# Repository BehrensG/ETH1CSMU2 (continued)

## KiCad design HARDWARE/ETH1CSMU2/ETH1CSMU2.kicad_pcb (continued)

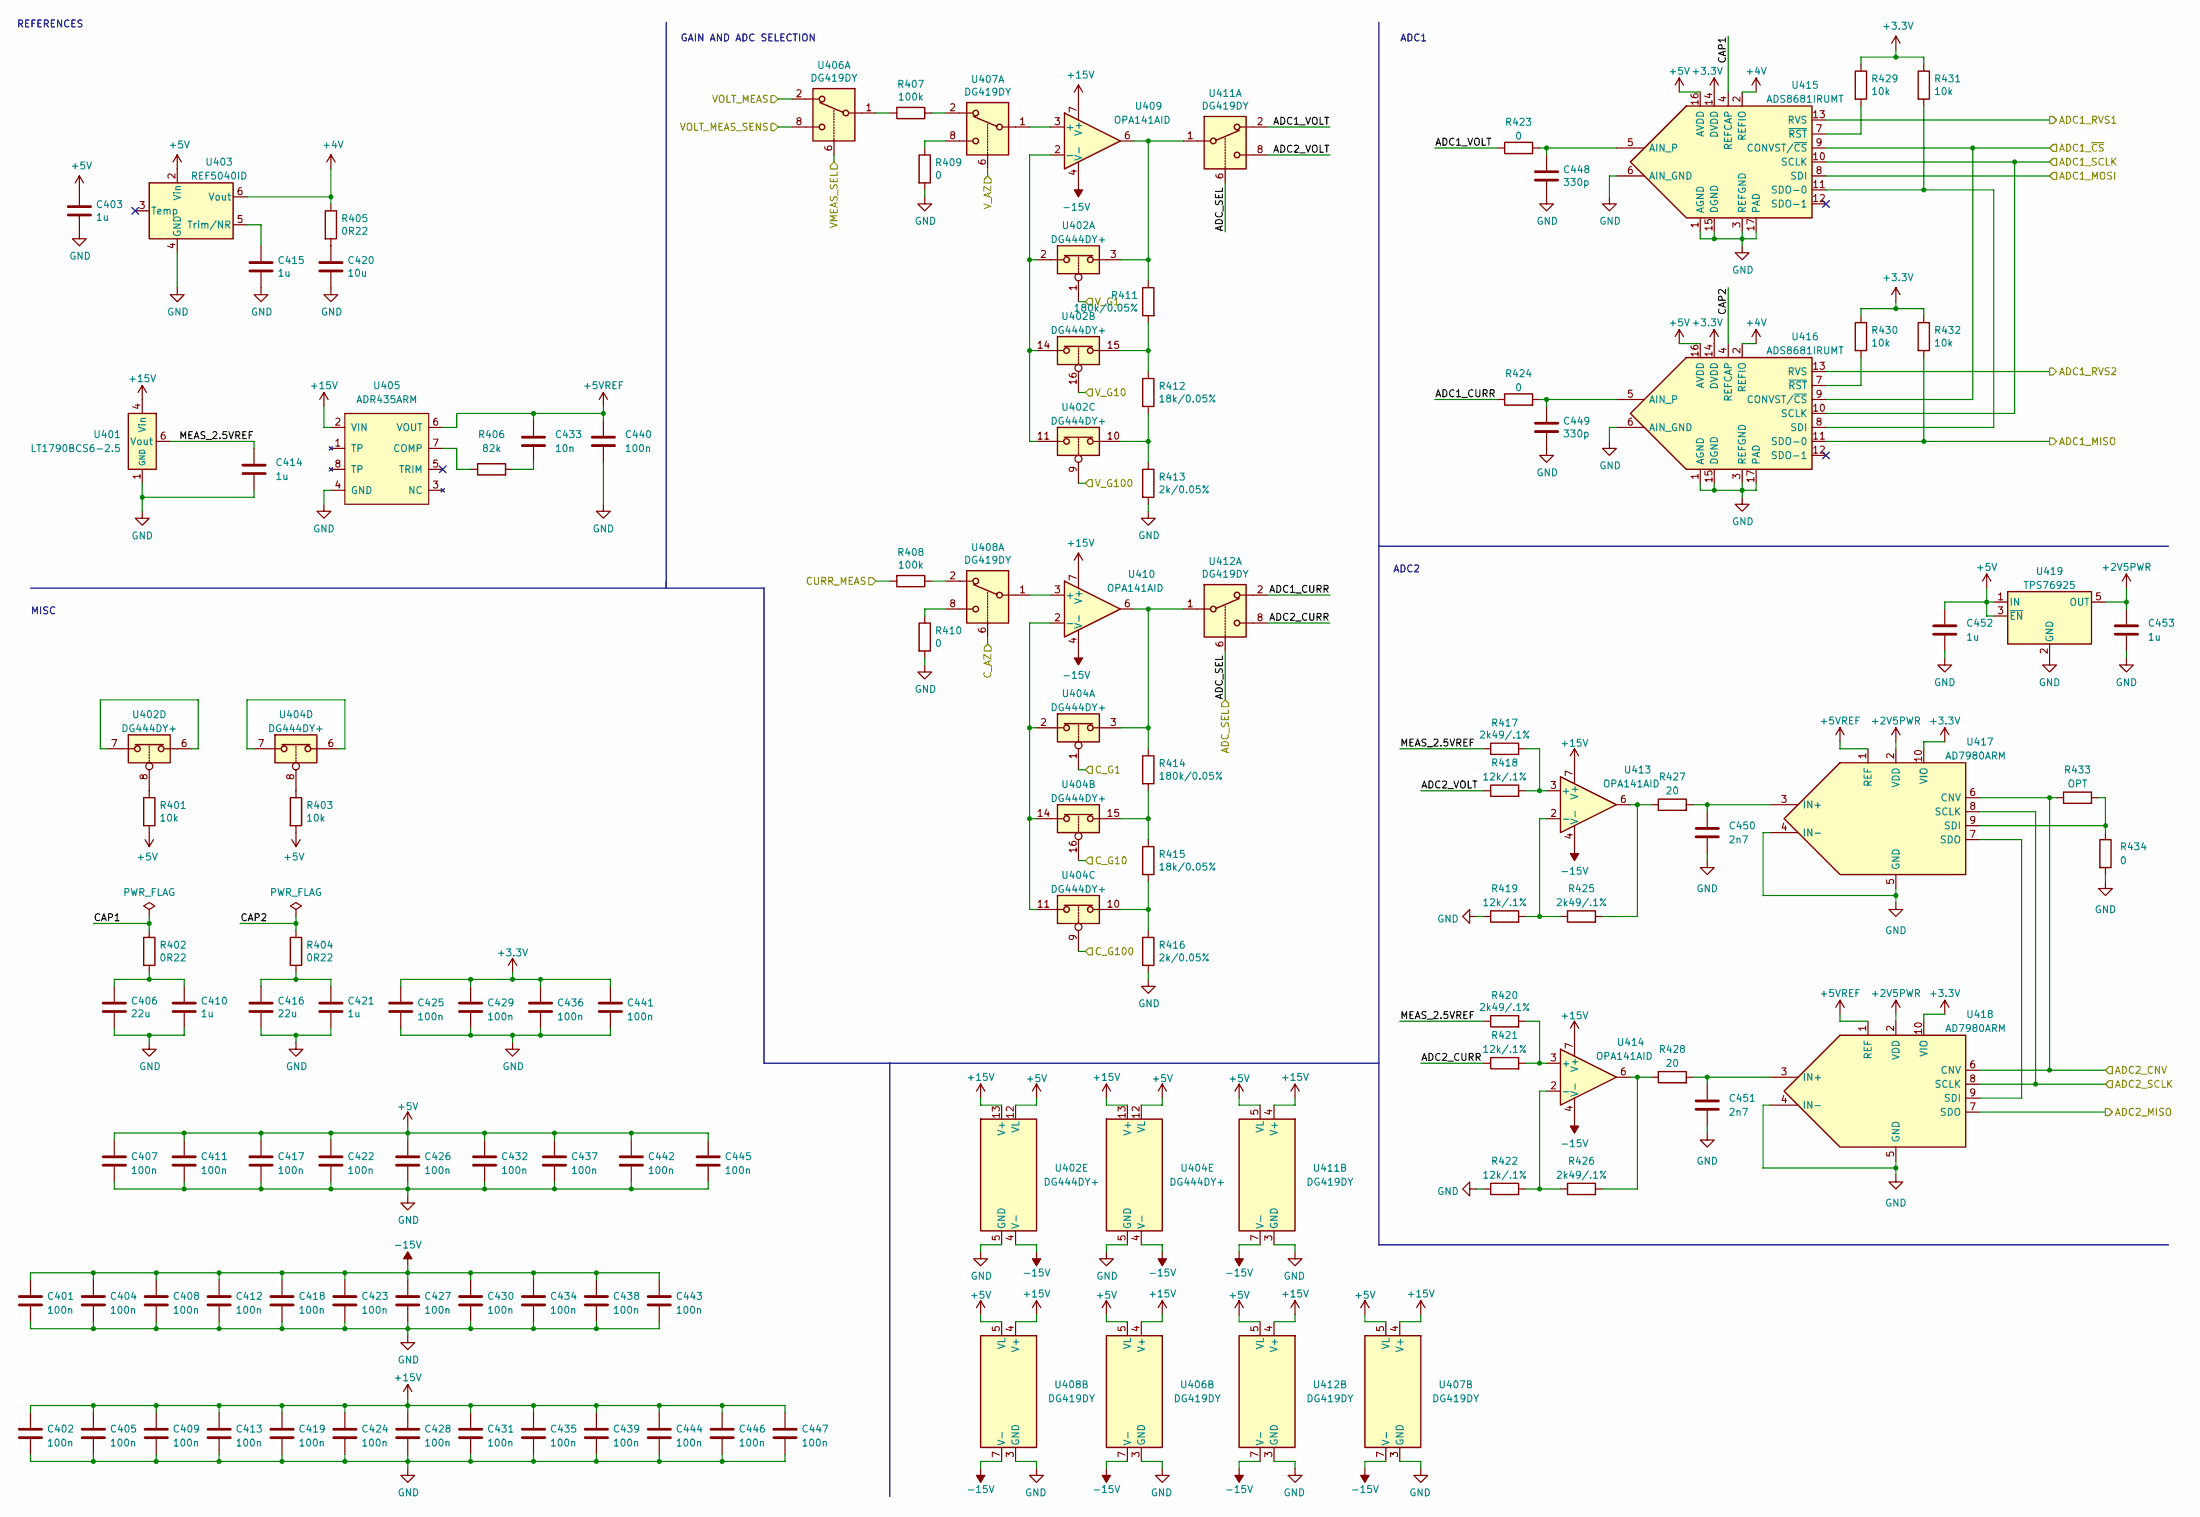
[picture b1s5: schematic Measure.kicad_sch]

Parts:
C401, C402, C404, C405, C407, C408, C409, C411, C412, C413, C417, C418, C419, C422, C423, C424, C425, C426, C427, C428, C429, C430, C431, C432, C434, C435, C436, C437, C438, C439, C440, C441, C442, C443, C444, C445, C446, C447: 100n; C_0603_1608Metric_Pad1.08x0.95mm_HandSolder
C403, C410, C414, C415, C421, C452, C453: 1u; C_0603_1608Metric_Pad1.08x0.95mm_HandSolder
C406, C416: 22u; R_0805_2012Metric_Pad1.20x1.40mm_HandSolder
C420: 10u; R_0805_2012Metric_Pad1.20x1.40mm_HandSolder
C433: 10n; C_0603_1608Metric_Pad1.08x0.95mm_HandSolder
C448, C449: 330p; C_0603_1608Metric_Pad1.08x0.95mm_HandSolder
C450, C451: 2n7; C_0603_1608Metric_Pad1.08x0.95mm_HandSolder
R401, R403, R429, R430, R431, R432: 10k; R_0603_1608Metric_Pad0.98x0.95mm_HandSolder
R402, R404, R405: 0R22; R_0603_1608Metric_Pad0.98x0.95mm_HandSolder
R406: 82k; R_0603_1608Metric_Pad0.98x0.95mm_HandSolder
R407, R408: 100k; R_0603_1608Metric_Pad0.98x0.95mm_HandSolder
R409, R410, R423, R424, R434: 0; R_0603_1608Metric_Pad0.98x0.95mm_HandSolder
R411, R414: 180k/0.05%; R_0603_1608Metric_Pad0.98x0.95mm_HandSolder
R412, R415: 18k/0.05%; R_0603_1608Metric_Pad0.98x0.95mm_HandSolder
R413, R416: 2k/0.05%; R_0603_1608Metric_Pad0.98x0.95mm_HandSolder
R417, R420, R425, R426: 2k49/.1%; R_0603_1608Metric_Pad0.98x0.95mm_HandSolder
R418, R419, R421, R422: 12k/.1%; R_0603_1608Metric_Pad0.98x0.95mm_HandSolder
R427, R428: 20; R_0603_1608Metric_Pad0.98x0.95mm_HandSolder
R433: OPT; R_0603_1608Metric_Pad0.98x0.95mm_HandSolder
U401: LT1790BCS6-2.5; TSOT-23-6
U402, U404: DG444DY+; SOIC-16_3.9x9.9mm_P1.27mm
U403: REF5040ID; SOIC-8_3.9x4.9mm_P1.27mm
U405: ADR435ARM; MSOP-8_3x3mm_P0.65mm
U406, U407, U408, U411, U412: DG419DY; SOIC-8_3.9x4.9mm_P1.27mm
U409, U410, U413, U414: OPA141AID; SOIC-8_3.9x4.9mm_P1.27mm
U415, U416: ADS8681IRUMT; QFN-16-1EP_4x4mm_P0.65mm_EP2.7x2.7mm
U417, U418: AD7980ARM; MSOP-10_3x3mm_P0.5mm
U419: TPS76925; SOT-23-5

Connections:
+2V5PWR: C453.1, U417.2 (VDD), U418.2 (VDD), U419.5 (OUT)
+4V: R405.1, U403.6 (Vout), U415.2 (REFIO), U416.2 (REFIO)
+5VREF: C433.1, C440.1, U405.6 (VOUT), U417.1 (REF), U418.1 (REF)
/Connect/VOLT_MEAS_SENS: U406.8; also elsewhere on the board
/Connect/VOUT_OUT: U406.2; also elsewhere on the board
/Control/C_AZ: U408.6; also elsewhere on the board
/Control/C_G1: U404.1; also elsewhere on the board
/Control/C_G10: U404.16; also elsewhere on the board
/Control/C_G100: U404.9; also elsewhere on the board
/Control/VMEAS_SEL: U406.6; also elsewhere on the board
/Control/V_AZ: U407.6; also elsewhere on the board
/Control/V_G1: U402.1; also elsewhere on the board
/Control/V_G10: U402.16; also elsewhere on the board
/Control/V_G100: U402.9; also elsewhere on the board
/Frontend/CURR_MEAS: R408.2; also elsewhere on the board
/MCU/ADC1_RVS1: U415.13 (RVS); also elsewhere on the board
/MCU/ADC1_RVS2: U416.13 (RVS); also elsewhere on the board
/MCU/SPI1_MISO: R432.2, U416.11 (SDO-0); also elsewhere on the board
/MCU/SPI1_MOSI: U415.8 (SDI); also elsewhere on the board
/MCU/SPI1_NSS: U415.9 (CONVST/~CS), U416.9 (CONVST/~CS); also elsewhere on the board
/MCU/SPI1_SCK: U415.10 (SCLK), U416.10 (SCLK); also elsewhere on the board
/MCU/SPI4_MISO: U418.7 (SDO); also elsewhere on the board
/MCU/SPI4_NSS: R433.1, U417.6 (CNV), U418.6 (CNV); also elsewhere on the board
/MCU/SPI4_SCK: U417.8 (SCLK), U418.8 (SCLK); also elsewhere on the board
/Measure/ADC1_CURR: R424.1, U412.2
/Measure/ADC1_VOLT: R423.1, U411.2
/Measure/ADC2_CURR: R421.1, U412.8
/Measure/ADC2_VOLT: R418.1, U411.8
/Measure/ADC_SEL: U411.6, U412.6; also elsewhere on the board
/Measure/CAP1: R402.1, U415.4 (REFCAP)
/Measure/CAP2: R404.1, U416.4 (REFCAP)
/Measure/MEAS_2.5VREF: C414.1, R417.1, R420.1, U401.6 (Vout)
unnamed: C406.1, C410.1, R402.2
unnamed: C415.1, U403.5 (Trim/NR)
unnamed: C416.1, C421.1, R404.2
unnamed: C420.1, R405.2
unnamed: C433.2, R406.2
unnamed: C448.1, R423.2, U415.5 (AIN_P)
unnamed: C449.1, R424.2, U416.5 (AIN_P)
unnamed: C450.1, R427.2, U417.3 (IN+)
unnamed: C451.1, R428.2, U418.3 (IN+)
unnamed: R401.1, U402.8
unnamed: R403.1, U404.8
unnamed: R406.1, U405.7 (COMP)
unnamed: R407.1, U407.2
unnamed: R407.2, U406.1
unnamed: R408.1, U408.2
unnamed: R409.1, U407.8
unnamed: R410.1, U408.8
unnamed: R411.1, U402.3, U409.6, U411.1
unnamed: R411.2, R412.1, U402.15
unnamed: R412.2, R413.1, U402.10
unnamed: R414.1, U404.3, U410.6, U412.1
unnamed: R414.2, R415.1, U404.15
unnamed: R415.2, R416.1, U404.10
unnamed: R417.2, R418.2, U413.3 (+)
unnamed: R419.2, R425.1, U413.2 (-)
unnamed: R420.2, R421.2, U414.3 (+)
unnamed: R422.2, R426.1, U414.2 (-)
unnamed: R425.2, R427.1, U413.6
unnamed: R426.2, R428.1, U414.6
unnamed: R429.2, U415.7 (~RST)
unnamed: R430.2, U416.7 (~RST)
unnamed: R431.2, U415.11 (SDO-0), U416.8 (SDI)
unnamed: R433.2, R434.1, U417.9 (SDI)
unnamed: U402.6, U402.7
unnamed: U402.2, U402.11, U402.14, U409.2 (-)
unnamed: U404.6, U404.7
unnamed: U404.2, U404.11, U404.14, U410.2 (-)
unnamed: U407.1, U409.3 (+)
unnamed: U408.1, U410.3 (+)
unnamed: U417.7 (SDO), U418.9 (SDI)

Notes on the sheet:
MISC
ADC1
ADC2
GAIN AND ADC SELECTION
REFERENCES

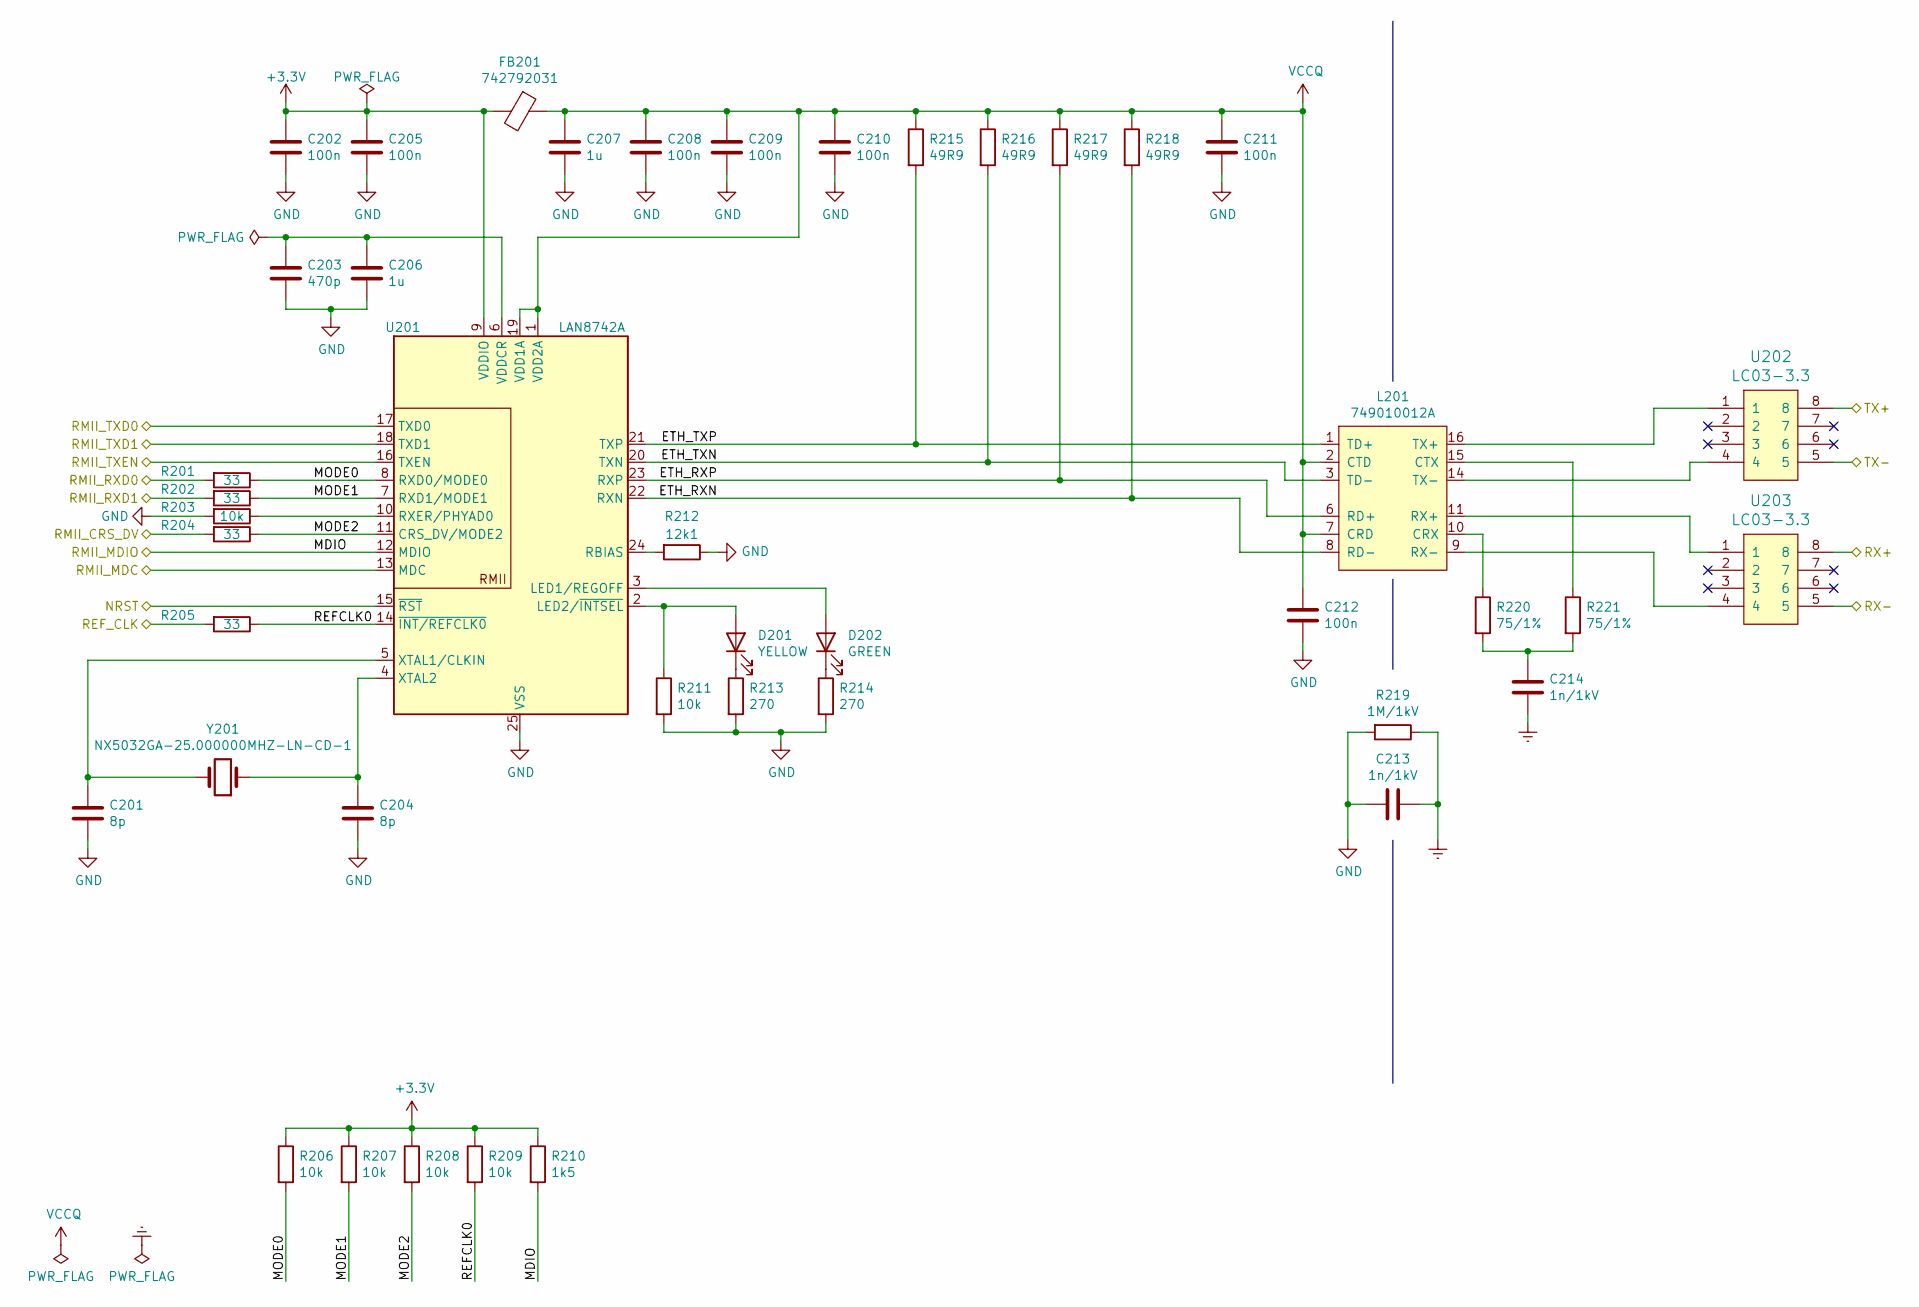
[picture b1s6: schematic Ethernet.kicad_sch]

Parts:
C201, C204: 8p; C_0603_1608Metric_Pad1.08x0.95mm_HandSolder
C202, C205, C208, C209, C210, C211, C212: 100n; C_0603_1608Metric_Pad1.08x0.95mm_HandSolder
C203: 470p; C_0603_1608Metric_Pad1.08x0.95mm_HandSolder
C206, C207: 1u; C_0603_1608Metric_Pad1.08x0.95mm_HandSolder
C213, C214: 1n/1kV; C_1206_3216Metric_Pad1.33x1.80mm_HandSolder
D201: YELLOW; LED_0603_1608Metric_Pad1.05x0.95mm_HandSolder
D202: GREEN; LED_0603_1608Metric_Pad1.05x0.95mm_HandSolder
FB201: 742792031; L_0805_2012Metric_Pad1.15x1.40mm_HandSolder
L201: 749010012A
R201, R202, R204, R205: 33; R_0603_1608Metric_Pad0.98x0.95mm_HandSolder
R203, R206, R207, R208, R209, R211: 10k; R_0603_1608Metric_Pad0.98x0.95mm_HandSolder
R210: 1k5; R_0603_1608Metric_Pad0.98x0.95mm_HandSolder
R212: 12k1; R_0603_1608Metric_Pad0.98x0.95mm_HandSolder
R213, R214: 270; R_0603_1608Metric_Pad0.98x0.95mm_HandSolder
R215, R216, R217, R218: 49R9; R_0603_1608Metric_Pad0.98x0.95mm_HandSolder
R219: 1M/1kV; R_1206_3216Metric_Pad1.30x1.75mm_HandSolder
R220, R221: 75/1%; R_0603_1608Metric_Pad0.98x0.95mm_HandSolder
U201: LAN8742A; QFN-24-1EP_4x4mm_P0.5mm_EP2.6x2.6mm_ThermalVias
U202, U203: LC03-3.3; SO8E
Y201: NX5032GA-25.000000MHZ-LN-CD-1; NX5032GA

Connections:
/Connect/RX+: U203.8; also elsewhere on the board
/Connect/RX-: U203.5; also elsewhere on the board
/Connect/TX+: U202.8; also elsewhere on the board
/Connect/TX-: U202.5; also elsewhere on the board
/Ethernet/ETH_RXN: L201.8 (RD-), R218.2, U201.22 (RXN)
/Ethernet/ETH_RXP: L201.6 (RD+), R217.2, U201.23 (RXP)
/Ethernet/ETH_TXN: L201.3 (TD-), R216.2, U201.20 (TXN)
/Ethernet/ETH_TXP: L201.1 (TD+), R215.2, U201.21 (TXP)
/Ethernet/MDIO: R210.2, U201.12 (MDIO); also elsewhere on the board
/Ethernet/MODE0: R201.1, R206.2, U201.8 (RXD0/MODE0)
/Ethernet/MODE1: R202.1, R207.2, U201.7 (RXD1/MODE1)
/Ethernet/MODE2: R204.1, R208.2, U201.11 (CRS_DV/MODE2)
/Ethernet/REFCLK0: R205.1, R209.2, U201.14 (~INT/REFCLK0)
/Ethernet/REF_CLK: R205.2; also elsewhere on the board
/Ethernet/RMII_CRS_DV: R204.2; also elsewhere on the board
/Ethernet/RMII_MDC: U201.13 (MDC); also elsewhere on the board
/Ethernet/RMII_RXD0: R201.2; also elsewhere on the board
/Ethernet/RMII_RXD1: R202.2; also elsewhere on the board
/Ethernet/RMII_TXD0: U201.17 (TXD0); also elsewhere on the board
/Ethernet/RMII_TXD1: U201.18 (TXD1); also elsewhere on the board
/Ethernet/RMII_TXEN: U201.16 (TXEN); also elsewhere on the board
/MCU/NRST: U201.15 (~RST); also elsewhere on the board
Earth: C213.1, C214.2, R219.1; also elsewhere on the board
unnamed: C201.1, U201.5 (XTAL1/CLKIN), Y201.2
unnamed: C203.1, C206.1, U201.6 (VDDCR)
unnamed: C204.1, U201.4 (XTAL2), Y201.1
unnamed: C214.1, R220.2, R221.2
unnamed: D201.1 (K), R213.1
unnamed: D201.2 (A), R211.1, U201.2 (LED2/~INTSEL)
unnamed: D202.1 (K), R214.1
unnamed: D202.2 (A), U201.3 (LED1/REGOFF)
unnamed: L201.9 (RX-), U203.4
unnamed: L201.10 (CRX), R220.1
unnamed: L201.11 (RX+), U203.1
unnamed: L201.14 (TX-), U202.4
unnamed: L201.15 (CTX), R221.1
unnamed: L201.16 (TX+), U202.1
unnamed: R203.1, U201.10 (RXER/PHYAD0)
unnamed: R212.2, U201.24 (RBIAS)
VCCQ: C207.1, C208.1, C209.1, C210.1, C211.1, C212.1, FB201.1, L201.2 (CTD), L201.7 (CRD), R215.1, R216.1, R217.1, R218.1, U201.1 (VDD2A), U201.19 (VDD1A)

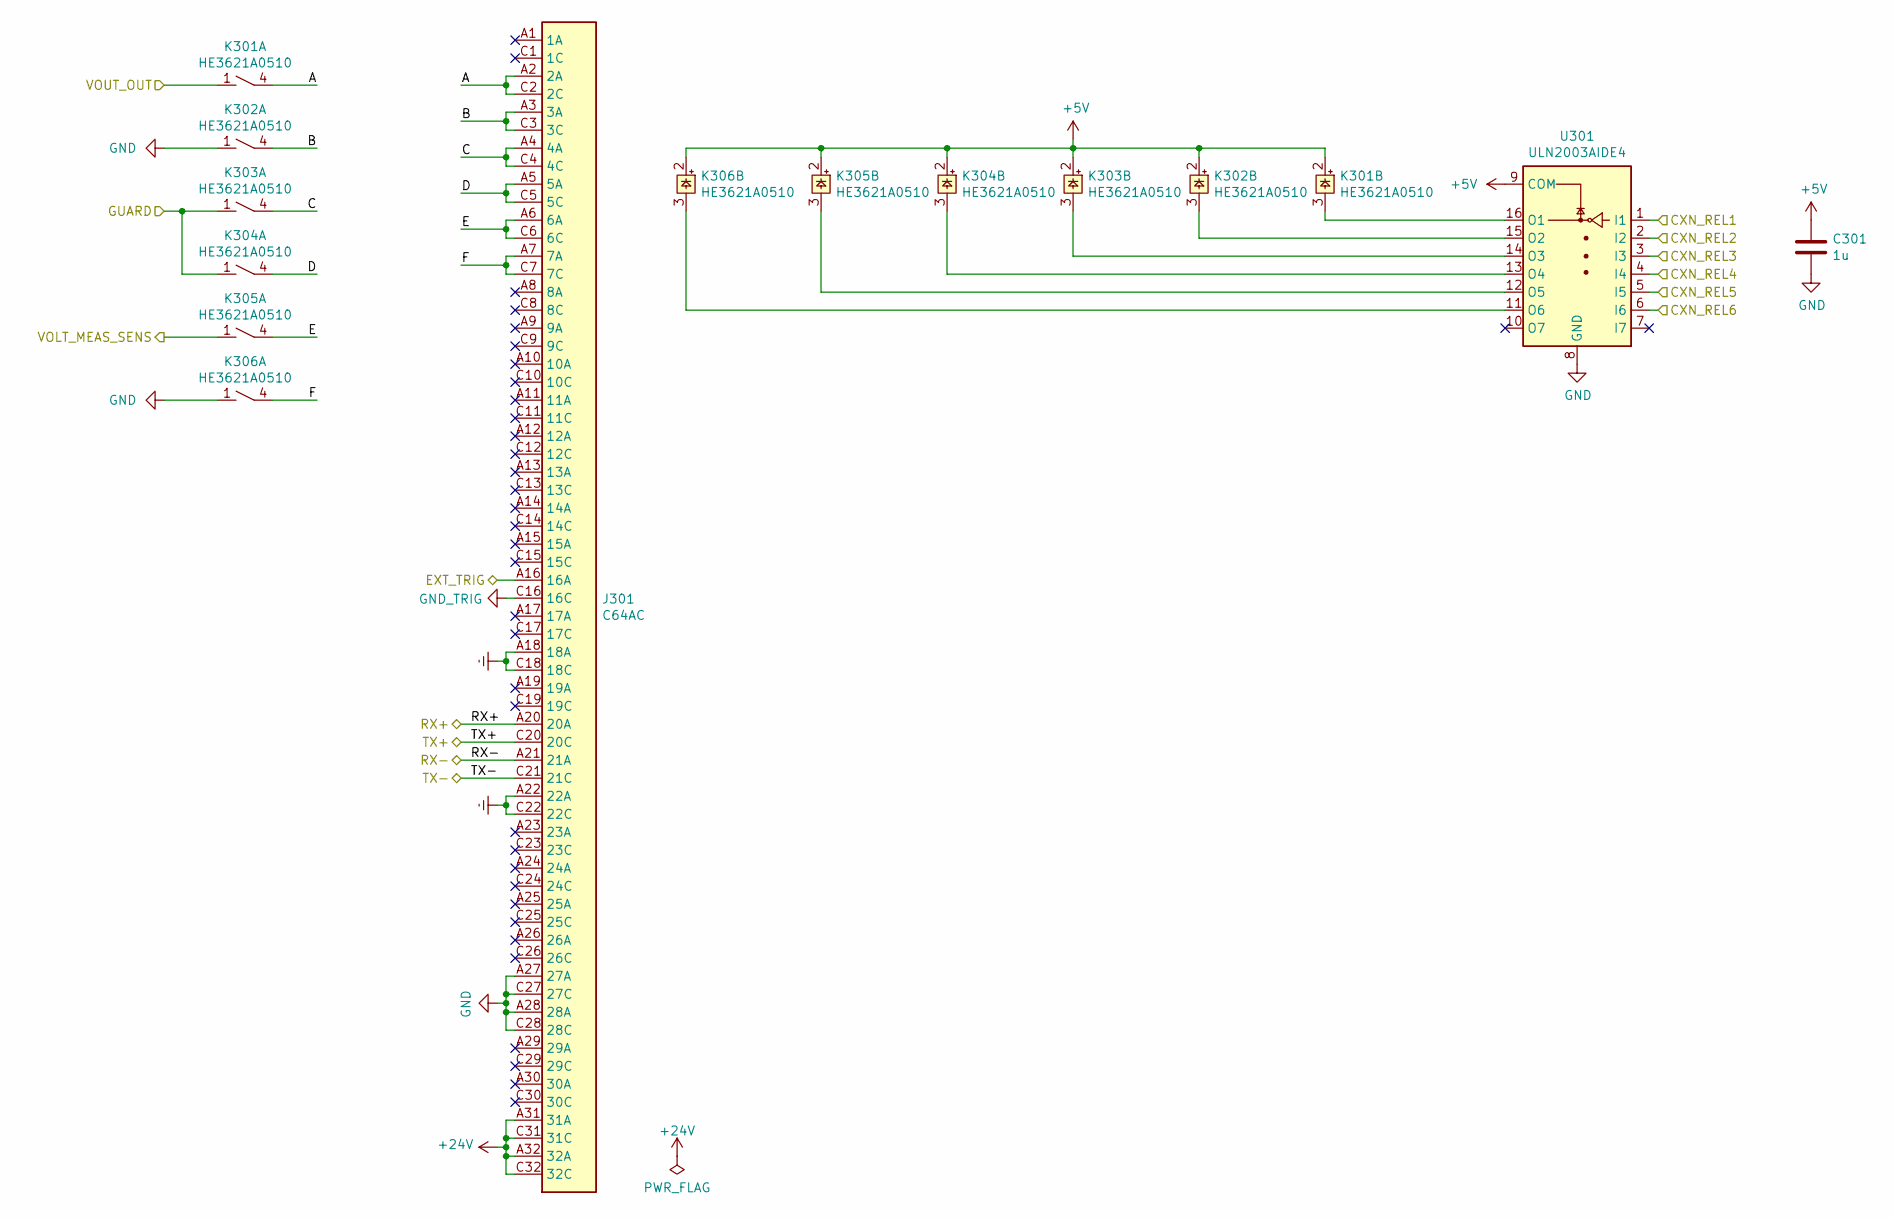
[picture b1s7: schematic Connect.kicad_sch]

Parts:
C301: 1u; C_0603_1608Metric_Pad1.08x0.95mm_HandSolder
J301: C64AC; Socket_DIN41612-CaseC1-AC-Male-64Pin-2rows
K301, K302, K303, K304, K305, K306: HE3621A0510; HE360_x-5050462-8
U301: ULN2003AIDE4; SOIC-16_3.9x9.9mm_P1.27mm

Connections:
+24V: J301.A31 (31A), J301.A32 (32A), J301.C31 (31C), J301.C32 (32C); also elsewhere on the board
/Connect/A: J301.A2 (2A), J301.C2 (2C), K301.4
/Connect/B: J301.A3 (3A), J301.C3 (3C), K302.4
/Connect/C: J301.A4 (4A), J301.C4 (4C), K303.4
/Connect/CXN_REL1: U301.1 (I1); also elsewhere on the board
/Connect/CXN_REL2: U301.2 (I2); also elsewhere on the board
/Connect/CXN_REL3: U301.3 (I3); also elsewhere on the board
/Connect/CXN_REL4: U301.4 (I4); also elsewhere on the board
/Connect/CXN_REL5: U301.5 (I5); also elsewhere on the board
/Connect/CXN_REL6: U301.6 (I6); also elsewhere on the board
/Connect/D: J301.A5 (5A), J301.C5 (5C), K304.4
/Connect/E: J301.A6 (6A), J301.C6 (6C), K305.4
/Connect/EXT_TRIG: J301.A16 (16A); also elsewhere on the board
/Connect/F: J301.A7 (7A), J301.C7 (7C), K306.4
/Connect/GUARD: K303.1, K304.1; also elsewhere on the board
/Connect/RX+: J301.A20 (20A); also elsewhere on the board
/Connect/RX-: J301.A21 (21A); also elsewhere on the board
/Connect/TX+: J301.C20 (20C); also elsewhere on the board
/Connect/TX-: J301.C21 (21C); also elsewhere on the board
/Connect/VOLT_MEAS_SENS: K305.1; also elsewhere on the board
/Connect/VOUT_OUT: K301.1; also elsewhere on the board
Earth: J301.A18 (18A), J301.A22 (22A), J301.C18 (18C), J301.C22 (22C); also elsewhere on the board
GND_TRIG: J301.C16 (16C); also elsewhere on the board
unnamed: K301.3, U301.16 (O1)
unnamed: K302.3, U301.15 (O2)
unnamed: K303.3, U301.14 (O3)
unnamed: K304.3, U301.13 (O4)
unnamed: K305.3, U301.12 (O5)
unnamed: K306.3, U301.11 (O6)

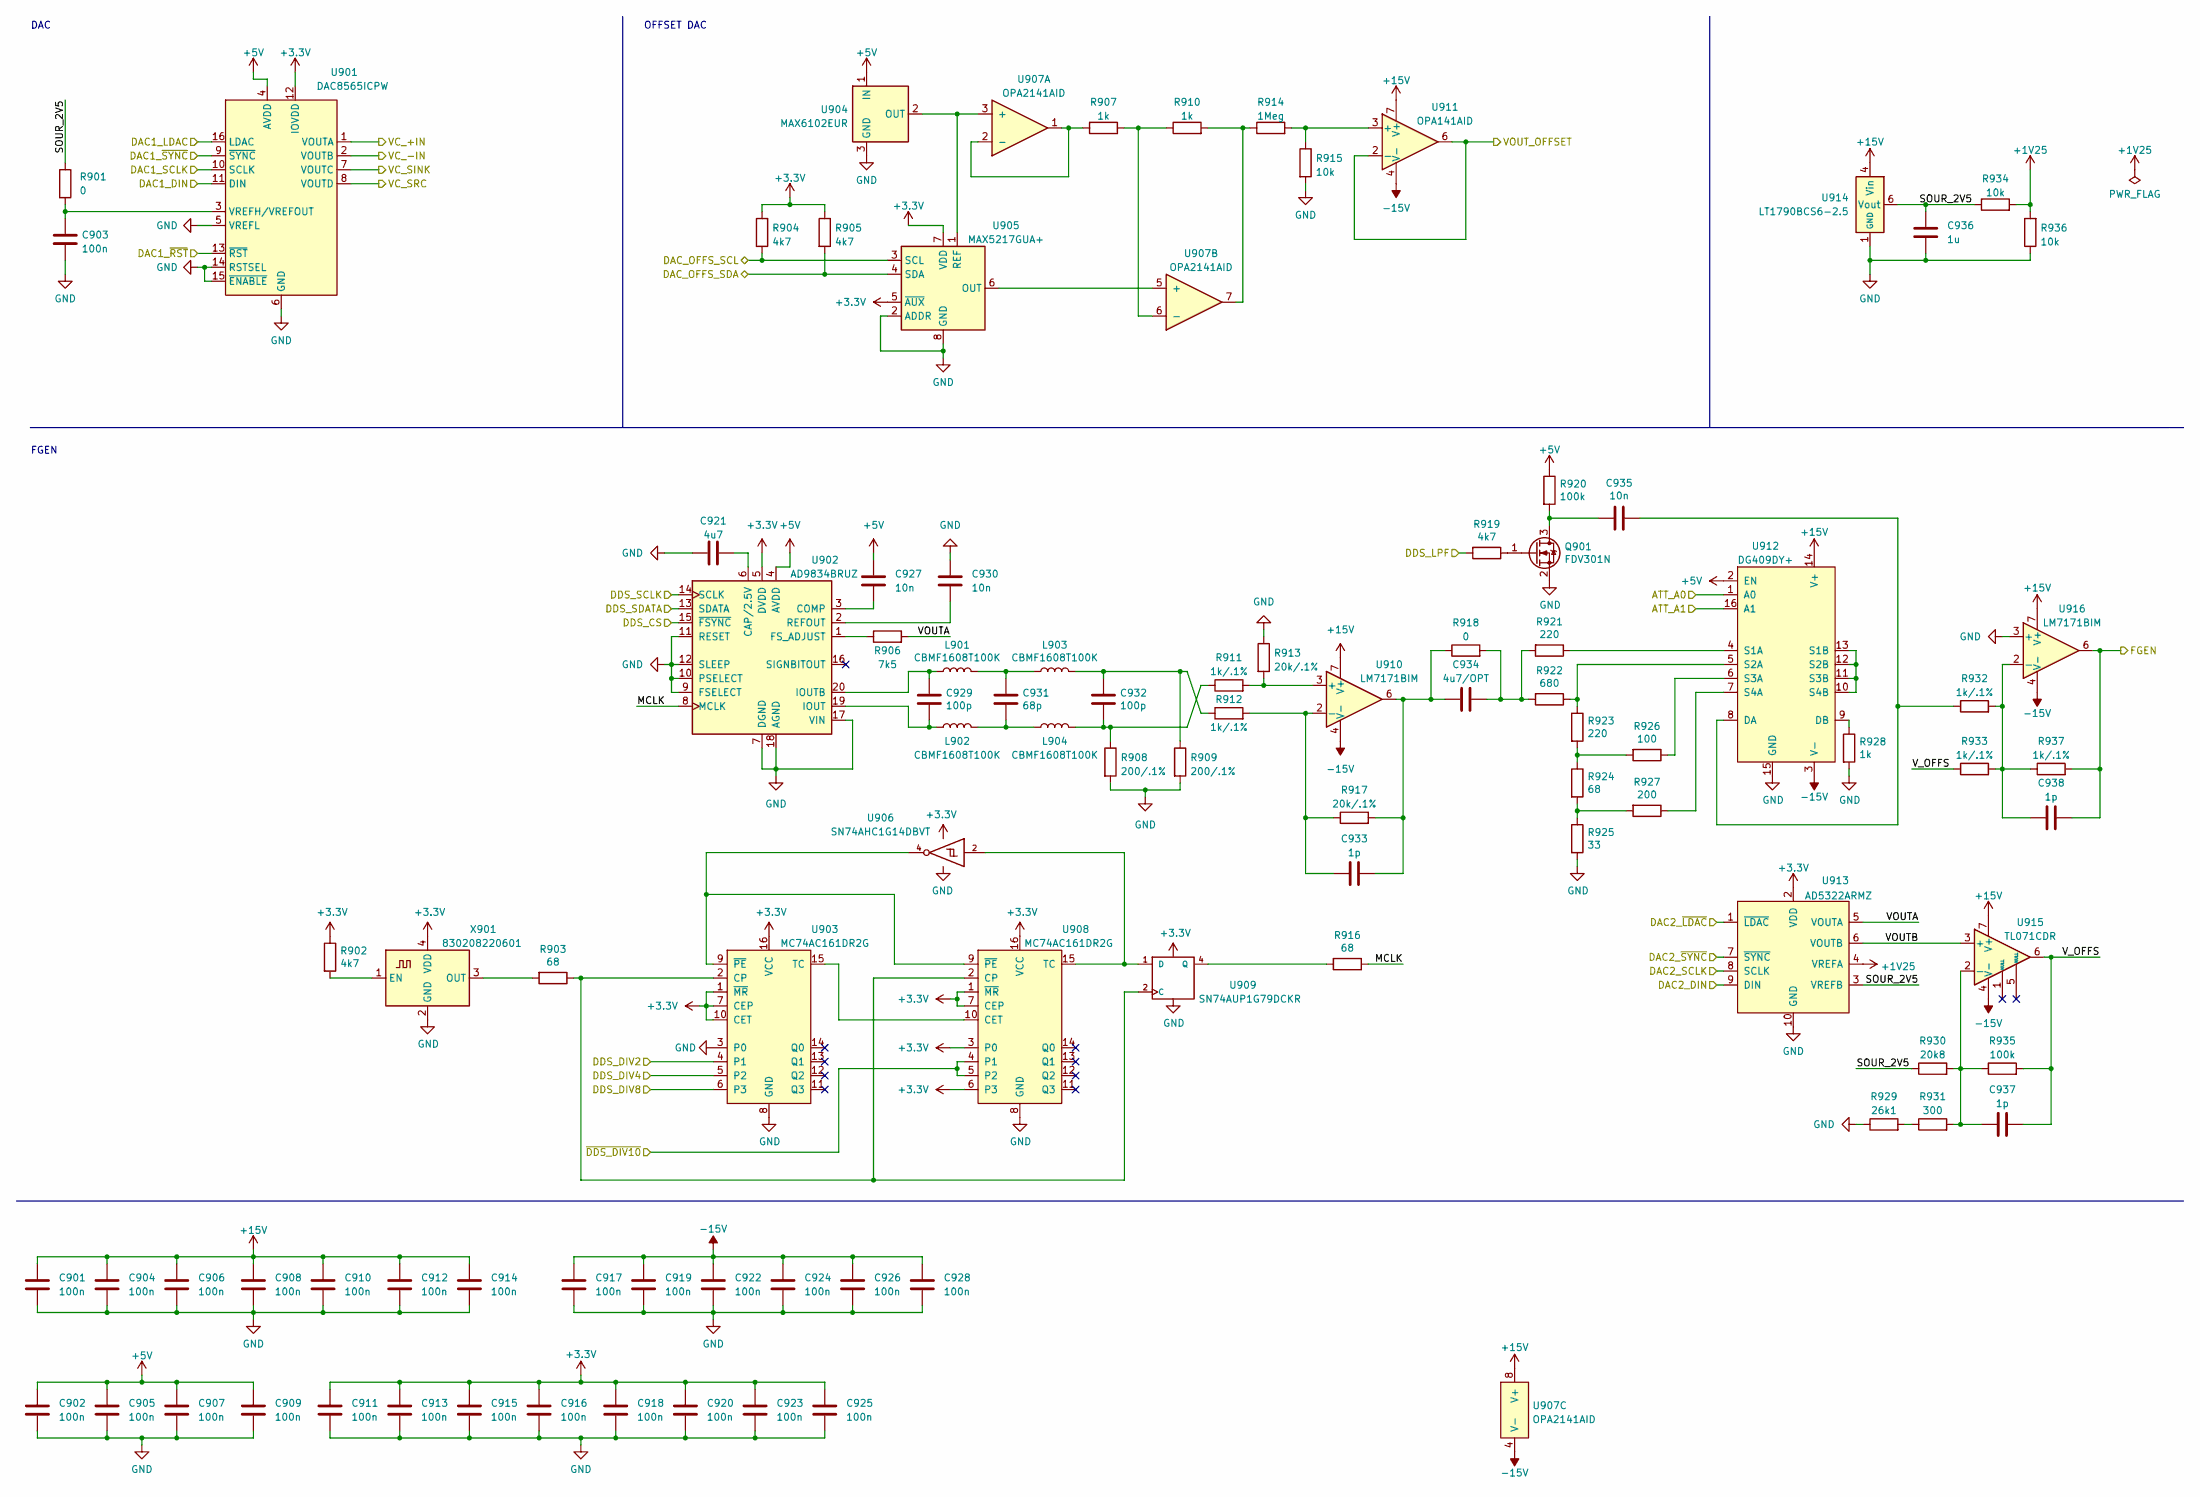
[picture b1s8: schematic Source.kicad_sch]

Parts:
C901, C902, C903, C904, C905, C906, C907, C908, C909, C910, C911, C912, C913, C914, C915, C916, C917, C918, C919, C920, C922, C923, C924, C925, C926, C928: 100n; C_0603_1608Metric_Pad1.08x0.95mm_HandSolder
C921: 4u7; C_0805_2012Metric_Pad1.18x1.45mm_HandSolder
C927, C930, C935: 10n; C_0603_1608Metric_Pad1.08x0.95mm_HandSolder
C929, C932: 100p; C_0603_1608Metric_Pad1.08x0.95mm_HandSolder
C931: 68p; C_0603_1608Metric_Pad1.08x0.95mm_HandSolder
C933, C937, C938: 1p; C_0603_1608Metric_Pad1.08x0.95mm_HandSolder
C934: 4u7/OPT; C_0805_2012Metric_Pad1.18x1.45mm_HandSolder
C936: 1u; C_0603_1608Metric_Pad1.08x0.95mm_HandSolder
L901, L902, L903, L904: CBMF1608T100K; L_0603_1608Metric_Pad1.05x0.95mm_HandSolder
Q901: FDV301N; SOT-23
R901, R918: 0; R_0603_1608Metric_Pad0.98x0.95mm_HandSolder
R902, R904, R905, R919: 4k7; R_0603_1608Metric_Pad0.98x0.95mm_HandSolder
R903, R916, R924: 68; R_0603_1608Metric_Pad0.98x0.95mm_HandSolder
R906: 7k5; R_0603_1608Metric_Pad0.98x0.95mm_HandSolder
R907, R910, R928: 1k; R_0603_1608Metric_Pad0.98x0.95mm_HandSolder
R908, R909: 200/.1%; R_0603_1608Metric_Pad0.98x0.95mm_HandSolder
R911, R912, R932, R933, R937: 1k/.1%; R_0603_1608Metric_Pad0.98x0.95mm_HandSolder
R913, R917: 20k/.1%; R_0603_1608Metric_Pad0.98x0.95mm_HandSolder
R914: 1Meg; R_0603_1608Metric_Pad0.98x0.95mm_HandSolder
R915, R934, R936: 10k; R_0603_1608Metric_Pad0.98x0.95mm_HandSolder
R920, R935: 100k; R_0603_1608Metric_Pad0.98x0.95mm_HandSolder
R921, R923: 220; R_0603_1608Metric_Pad0.98x0.95mm_HandSolder
R922: 680; R_0603_1608Metric_Pad0.98x0.95mm_HandSolder
R925: 33; R_0603_1608Metric_Pad0.98x0.95mm_HandSolder
R926: 100; R_0603_1608Metric_Pad0.98x0.95mm_HandSolder
R927: 200; R_0603_1608Metric_Pad0.98x0.95mm_HandSolder
R929: 26k1; R_0603_1608Metric_Pad0.98x0.95mm_HandSolder
R930: 20k8; R_0603_1608Metric_Pad0.98x0.95mm_HandSolder
R931: 300; R_0603_1608Metric_Pad0.98x0.95mm_HandSolder
U901: DAC8565ICPW; TSSOP-16_4.4x5mm_P0.65mm
U902: AD9834BRUZ; TSSOP-20_4.4x6.5mm_P0.65mm
U903, U908: MC74AC161DR2G; SOIC-16_3.9x9.9mm_P1.27mm
U904: MAX6102EUR; SOT-23
U905: MAX5217GUA+; MSOP-8_3x3mm_P0.65mm
U906: SN74AHC1G14DBVT; SOT-23-5_HandSoldering
U907: OPA2141AID; SOIC-8_3.9x4.9mm_P1.27mm
U909: SN74AUP1G79DCKR; SOT-353_SC-70-5_Handsoldering
U910, U916: LM7171BIM; SOIC-8_3.9x4.9mm_P1.27mm
U911: OPA141AID; SOIC-8_3.9x4.9mm_P1.27mm
U912: DG409DY+; SOIC-16_3.9x9.9mm_P1.27mm
U913: AD5322ARMZ; MSOP-10_3x3mm_P0.5mm
U914: LT1790BCS6-2.5; TSOT-23-6
U915: TL071CDR; SOIC-8_3.9x4.9mm_P1.27mm
X901: 830208220601; IQXO-791

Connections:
+1V25: R934.2, R936.2, U913.4 (VREFA)
/Control/ATT_A0: U912.1 (A0); also elsewhere on the board
/Control/ATT_A1: U912.16 (A1); also elsewhere on the board
/Control/DDS_LPF: R919.2; also elsewhere on the board
/Frontend/FGEN: C938.2, R937.2, U916.6; also elsewhere on the board
/Frontend/VC_+IN: U901.1 (VOUTA); also elsewhere on the board
/Frontend/VC_-IN: U901.2 (VOUTB); also elsewhere on the board
/Frontend/VC_SINK: U901.7 (VOUTC); also elsewhere on the board
/Frontend/VC_SRC: U901.8 (VOUTD); also elsewhere on the board
/Frontend/VOUT_OFFSET: U911.2 (-), U911.6; also elsewhere on the board
/MCU/DAC1_LDAC: U901.16 (LDAC); also elsewhere on the board
/MCU/DAC1_~RST: U901.13 (~RST); also elsewhere on the board
/MCU/DAC2_~LDAC: U913.1 (~LDAC); also elsewhere on the board
/MCU/DDS_DIV2: U903.4 (P1); also elsewhere on the board
/MCU/DDS_DIV4: U903.5 (P2); also elsewhere on the board
/MCU/DDS_DIV8: U903.6 (P3); also elsewhere on the board
/MCU/SENS_SCL: R904.2, U905.3 (SCL); also elsewhere on the board
/MCU/SENS_SDA: R905.2, U905.4 (SDA); also elsewhere on the board
/MCU/SPI2_MOSI: U901.11 (DIN); also elsewhere on the board
/MCU/SPI2_NSS: U901.9 (~SYNC); also elsewhere on the board
/MCU/SPI2_SCK: U901.10 (SCLK); also elsewhere on the board
/MCU/SPI3_MOSI: U902.13 (SDATA); also elsewhere on the board
/MCU/SPI3_NSS: U902.15 (~FSYNC); also elsewhere on the board
/MCU/SPI3_SCK: U902.14 (SCLK); also elsewhere on the board
/MCU/SPI5_MOSI: U913.9 (DIN); also elsewhere on the board
/MCU/SPI5_NSS: U913.7 (~SYNC); also elsewhere on the board
/MCU/SPI5_SCK: U913.8 (SCLK); also elsewhere on the board
/MCU/~DDS_DIV10: U908.4 (P1), U908.5 (P2); also elsewhere on the board
/Source/MCLK: R916.1, U902.8 (MCLK)
/Source/SOUR_2V5: C936.1, R901.1, R930.1, R934.1, U913.3 (VREFB), U914.6 (Vout)
/Source/VOUTA: R906.2, U913.5 (VOUTA)
/Source/VOUTB: U913.6 (VOUTB), U915.3 (+)
/Source/V_OFFS: C937.2, R933.1, R935.2, U915.6
unnamed: C903.1, R901.2, U901.3 (VREFH/VREFOUT)
unnamed: C921.2, U902.6 (CAP/2.5V)
unnamed: C927.2, U902.3 (COMP)
unnamed: C929.1, L901.1, U902.20 (IOUTB)
unnamed: C929.2, L902.1, U902.19 (IOUT)
unnamed: C930.2, U902.2 (REFOUT)
unnamed: C931.1, L901.2, L903.1
unnamed: C931.2, L902.2, L904.1
unnamed: C932.1, L903.2, R909.1, R912.1
unnamed: C932.2, L904.2, R908.1, R911.1
unnamed: C933.1, R912.2, R917.1, U910.2 (-)
unnamed: C933.2, C934.1, R917.2, R918.1, U910.6
unnamed: C934.2, R918.2, R921.2, R922.2
unnamed: C935.1, R932.1, U912.8 (DA)
unnamed: C935.2, Q901.3 (D), R920.2
unnamed: C937.1, R930.2, R931.2, R935.1, U915.2 (-)
unnamed: C938.1, R932.2, R933.2, R937.1, U916.2 (-)
unnamed: Q901.1 (G), R919.1
unnamed: R902.2, X901.1 (EN)
unnamed: R903.1, U903.2 (CP), U908.2 (CP), U909.2 (C)
unnamed: R903.2, X901.3 (OUT)
unnamed: R906.1, U902.1 (FS_ADJUST)
unnamed: R907.1, U907.1, U907.2 (-)
unnamed: R907.2, R910.1, U907.6 (-)
unnamed: R910.2, R914.1, U907.7
unnamed: R911.2, R913.2, U910.3 (+)
unnamed: R914.2, R915.1, U911.3 (+)
unnamed: R916.2, U909.4 (Q)
unnamed: R921.1, U912.4 (S1A)
unnamed: R922.1, R923.1, U912.5 (S2A)
unnamed: R923.2, R924.1, R926.2
unnamed: R924.2, R925.1, R927.2
unnamed: R926.1, U912.6 (S3A)
unnamed: R927.1, U912.7 (S4A)
unnamed: R928.1, U912.9 (DB)
unnamed: R929.2, R931.1
unnamed: U903.9 (~PE), U906.4, U908.9 (~PE)
unnamed: U903.15 (TC), U908.10 (CET)
unnamed: U904.2 (OUT), U905.1 (REF), U907.3 (+)
unnamed: U905.6 (OUT), U907.5 (+)
unnamed: U906.2, U908.15 (TC), U909.1 (D)
unnamed: U912.10 (S4B), U912.11 (S3B), U912.12 (S2B), U912.13 (S1B)

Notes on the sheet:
FGEN
OFFSET DAC
DAC

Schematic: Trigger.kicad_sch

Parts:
C701, C703, C704, C706, C708: 100n; C_0603_1608Metric_Pad1.08x0.95mm_HandSolder
C702, C705, C707: 1u; C_0603_1608Metric_Pad1.08x0.95mm_HandSolder
C709: 47p; C_0603_1608Metric_Pad1.08x0.95mm_HandSolder
D701: BAV99; SOT-23
D702: SMBJ5.0A; D_SMB
D703: SD36C-01FTG; D_SOD-323_HandSoldering
L701: CW252016-R33G; CW252016
R701: 10k; R_0603_1608Metric_Pad0.98x0.95mm_HandSolder
R702: 14k7; R_0603_1608Metric_Pad0.98x0.95mm_HandSolder
R703: 100; R_0603_1608Metric_Pad0.98x0.95mm_HandSolder
R704: 1k; R_0603_1608Metric_Pad0.98x0.95mm_HandSolder
R705: 47; R_0603_1608Metric_Pad0.98x0.95mm_HandSolder
R706: 51R1; R_0603_1608Metric_Pad0.98x0.95mm_HandSolder
U701: TXB0104PW; TSSOP-14_4.4x5mm_P0.65mm
U702: ADuM5402; SOIC-16W_7.5x10.3mm_P1.27mm
U703: 74AC125; TSSOP-14_4.4x5mm_P0.65mm

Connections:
+5V_TRIG: C706.1, C707.1, C708.1, R704.1, U702.10 (VSEL), U702.16 (VISO), U703.14 (VCC)
/Connect/EXT_TRIG: C709.1, D703.1 (A1), L701.1; also elsewhere on the board
/MCU/TRIG_EN: U701.2 (A1); also elsewhere on the board
/MCU/TRIG_IN: U701.4 (A3); also elsewhere on the board
/MCU/TRIG_OUT: U701.3 (A2); also elsewhere on the board
/Trigger/EXT_TRIG_SIGN: R702.1, U702.12 (VIC), U703.3 (O)
/Trigger/TRIG_OUT_EN: U702.14 (VOA), U703.4 (EN), U703.10 (EN), U703.13 (EN)
/Trigger/TRIG_OUT_SIGN: U702.13 (VOB), U703.5 (D), U703.9 (D), U703.12 (D)
GND_TRIG: C706.2, C707.2, C708.2, D701.1 (K), D702.2 (A), D703.2 (A2), R706.2, U702.9 (GNDISO), U702.15 (GNDISO), U703.1 (EN), U703.7 (GND); also elsewhere on the board
unnamed: C709.2, R706.1
unnamed: D701.2 (A), D702.1 (K), R704.2
unnamed: D701.3 (K), R703.2, R705.1, U703.6 (O), U703.8 (O), U703.11 (O)
unnamed: L701.2, R705.2
unnamed: R701.2, U701.8 (OE)
unnamed: R702.2, R703.1, U703.2 (D)
unnamed: U701.11 (B3), U702.5 (VOC)
unnamed: U701.12 (B2), U702.4 (VIB)
unnamed: U701.13 (B1), U702.3 (VIA)

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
